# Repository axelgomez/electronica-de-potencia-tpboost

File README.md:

# electronica-de-potencia-tpboost

## Por un lado tenemos el tp flyback (en carpeta homónima)
.pro del Kicad 5.1.X

## Por otro lado tenemos el tp boost
.pro del Kicad 5.1.X

### Nuevas medidas de los componentes a cambiar en el pcb
La primer medida siempre es la distancia entre patas
OK - RL mide 5,5cm por 1cm de ancho y 1cm de alto (1mm de diametro de las patas)
OK - Pines de 2,54mm comunes para popner con jumpers 
OK - Diodo schottky 1,5cm
OK - Capacitor de 470uF 0,5cm. El encapsulado mide 1cm de diametro
OK - Capacitor de 1000uF 0,5cm. El encapsulado mide 1,4cm de diametro
OK - Capacitor de 1nF 0,3cm.
OK - Capacitor de 100nF 0,5cm.
OK - Capacitor de 100pF y 470pF 0,3cm

### Tareas adicionales a realizar:
OK - Agregar resistencias del tamaño de las comunes (1/4W) para sensar corriente en:
	+ Bobina
	+ Capacitor de salida
	+ Diodo schottky
- Hacer agujeros de 3mm para los soportes

## ChangeLog
### Version 28-05-2019 21:10
Se redujo la placa de 10cm x 20cm a 5cm x 10cm.

### Version 28-05-2019 21:55
Se emprolijó el puente de la realimentación, que habia quedado sobre una RQ1.

### Version 29-09-2019 22:52
Se creó el .pro para el tp de flyback y se organizó cada tp en una carpeta diferente

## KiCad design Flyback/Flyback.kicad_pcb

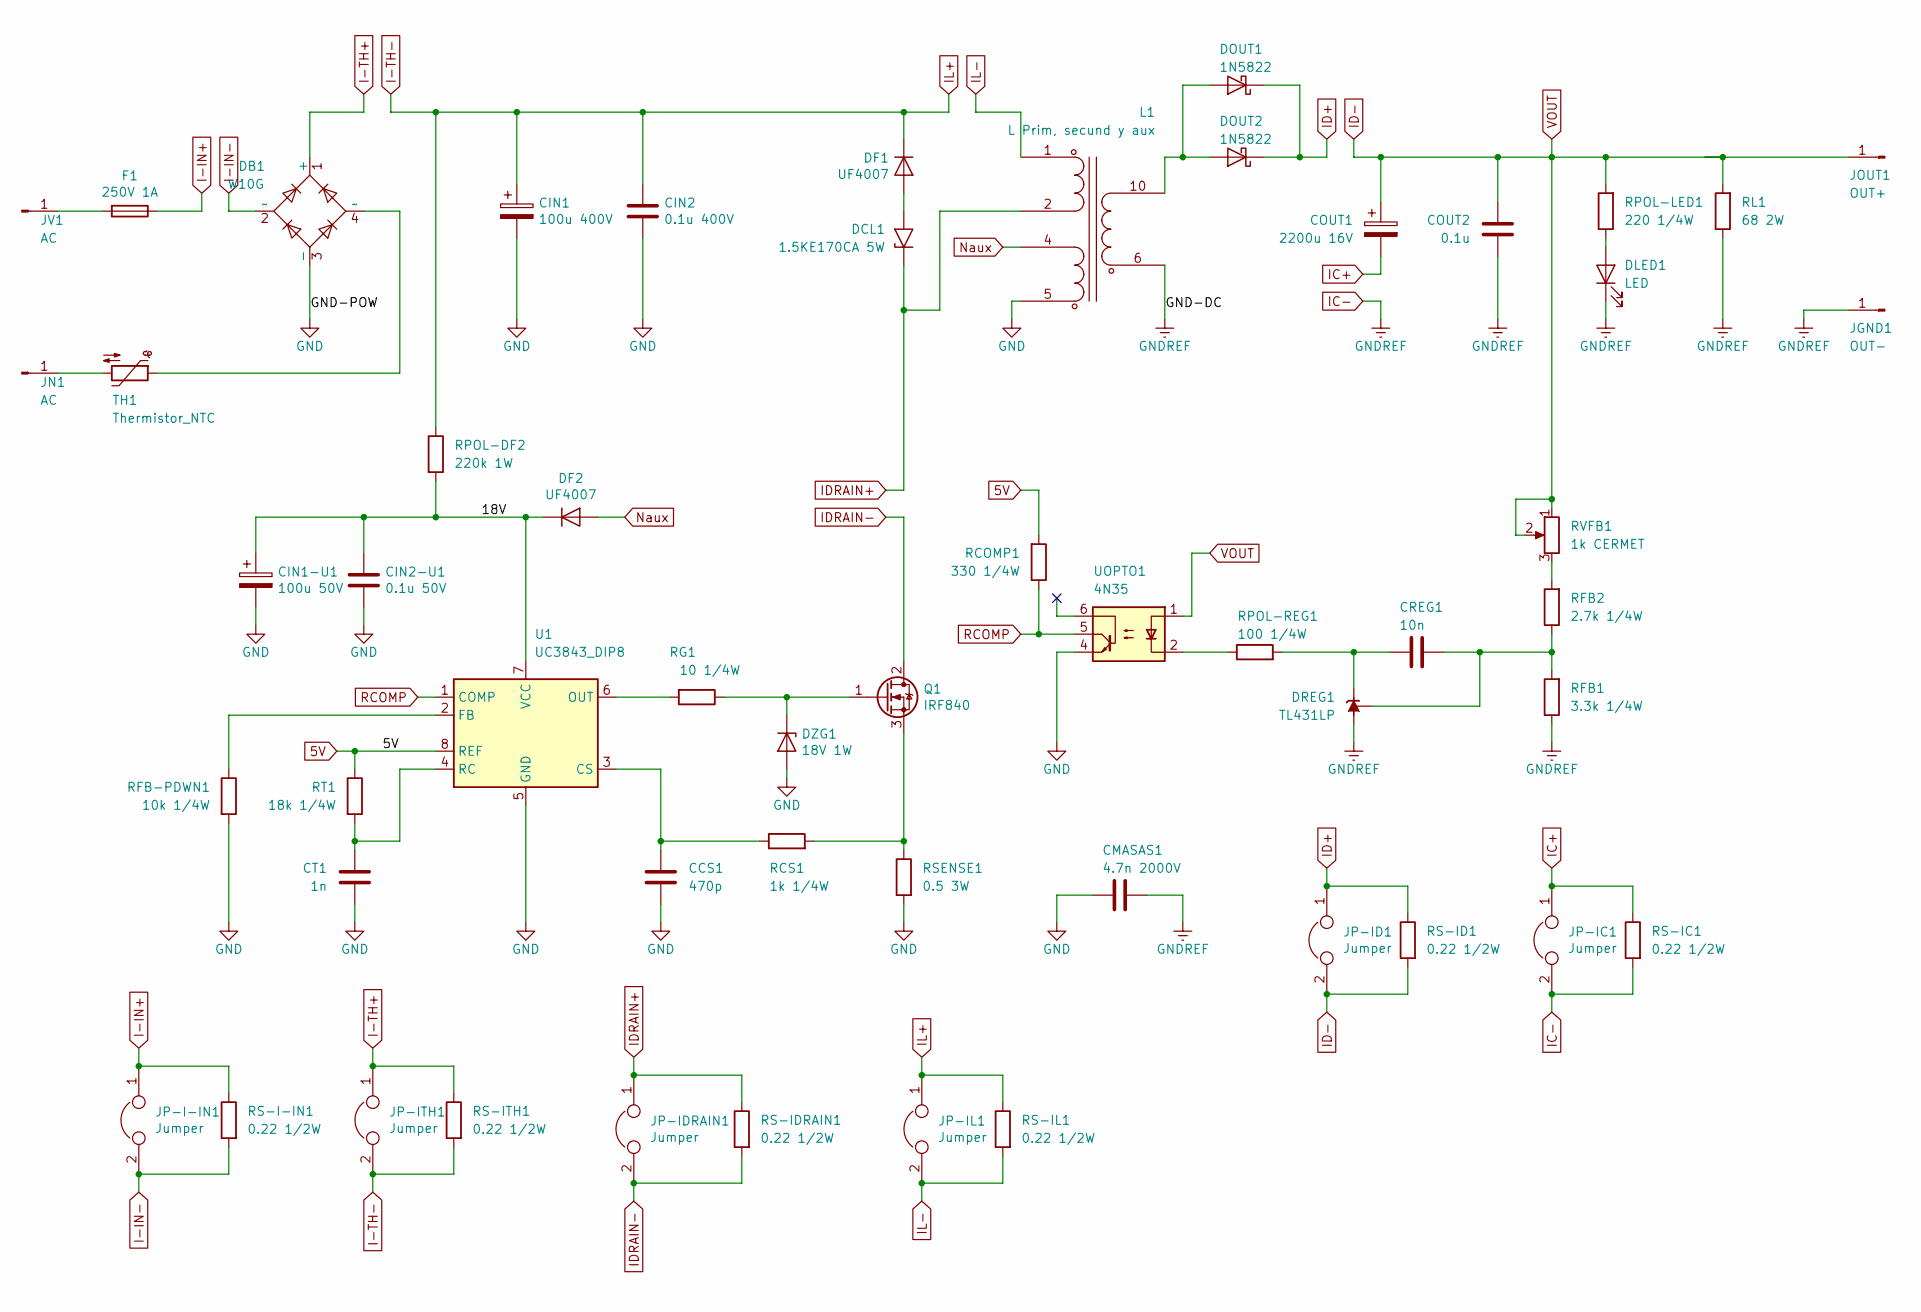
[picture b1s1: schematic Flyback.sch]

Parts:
CCS1: 470p; C_Disc_D3.8mm_W2.6mm_P2.50mm
CIN1: 100u 400V; C_Radial_D18.0mm_H35.5mm_P7.50mm
CIN1-U1: 100u 50V; C_Radial_D8.0mm_H11.5mm_P3.50mm
CIN2: 0.1u 400V; C_Axial_L3.8mm_D2.6mm_P12.50mm_Horizontal
CIN2-U1: 0.1u 50V; C_Disc_D3.8mm_W2.6mm_P2.50mm
CMASAS1: 4.7n 2000V; C_Rect_L9.0mm_W3.2mm_P7.50mm_MKT
COUT1: 2200u 16V; C_Radial_D12.5mm_H25.0mm_P5.00mm
COUT2: 0.1u; C_Disc_D3.8mm_W2.6mm_P2.50mm
CREG1: 10n; C_Rect_L7.2mm_W2.5mm_P5.00mm_FKS2_FKP2_MKS2_MKP2
CT1: 1n; C_Disc_D3.8mm_W2.6mm_P2.50mm
DB1: W10G; PuenteDiodos
DCL1: 1.5KE170CA 5W; D_DO-201AE_P15.24mm_Horizontal
DF1: UF4007; D_DO-41_SOD81_P10.16mm_Horizontal
DF2: UF4007; D_DO-41_SOD81_P12.70mm_Horizontal
DLED1: LED; LED_D5.0mm
DOUT1, DOUT2: 1N5822; D_DO-201AD_P15.24mm_Horizontal
DREG1: TL431LP; TO-92L_Inline_Wide
DZG1: 18V 1W; D_DO-35_SOD27_P10.16mm_Horizontal
F1: 250V 1A; Fuseholder_Cylinder-5x20mm_Stelvio-Kontek_PTF78_Horizontal_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
JGND1: OUT-; Banana_Jack_1Pin
JN1: AC; Banana_Jack_1Pin
JOUT1: OUT+; Banana_Jack_1Pin
JP-I-IN1: Jumper; PinHeader_1x02_P2.54mm_Vertical
JP-IC1: Jumper; PinHeader_1x02_P2.54mm_Vertical
JP-ID1: Jumper; PinHeader_1x02_P2.54mm_Vertical
JP-IDRAIN1: Jumper; PinHeader_1x02_P2.54mm_Vertical
JP-IL1: Jumper; PinHeader_1x02_P2.54mm_Vertical
JP-ITH1: Jumper; PinHeader_1x02_P2.54mm_Vertical
JV1: AC; Banana_Jack_1Pin
L1: L Prim, secund y aux; Trafo-E30157
Q1: IRF840; TO-220-3_Vertical
RCOMP1: 330 1/4W; R_Axial_DIN0207_L6.3mm_D2.5mm_P10.16mm_Horizontal
RCS1: 1k 1/4W; R_Axial_DIN0207_L6.3mm_D2.5mm_P10.16mm_Horizontal
RFB1: 3.3k 1/4W; R_Axial_DIN0309_L9.0mm_D3.2mm_P15.24mm_Horizontal
RFB2: 2.7k 1/4W; R_Axial_DIN0309_L9.0mm_D3.2mm_P15.24mm_Horizontal
RFB-PDWN1: 10k 1/4W; R_Axial_DIN0207_L6.3mm_D2.5mm_P10.16mm_Horizontal
RG1: 10 1/4W; R_Axial_DIN0207_L6.3mm_D2.5mm_P10.16mm_Horizontal
RL1: 68 2W; RCarga30mm
RPOL-DF2: 220k 1W; R12,5
RPOL-LED1: 220 1/4W; R_Axial_DIN0207_L6.3mm_D2.5mm_P10.16mm_Horizontal
RPOL-REG1: 100 1/4W; R_Axial_DIN0309_L9.0mm_D3.2mm_P15.24mm_Horizontal
RS-I-IN1: 0.22 1/2W; R_Axial_DIN0309_L9.0mm_D3.2mm_P15.24mm_Horizontal
RS-IC1: 0.22 1/2W; R_Axial_DIN0309_L9.0mm_D3.2mm_P15.24mm_Horizontal
RS-ID1: 0.22 1/2W; R_Axial_DIN0309_L9.0mm_D3.2mm_P15.24mm_Horizontal
RS-IDRAIN1: 0.22 1/2W; R_Axial_DIN0309_L9.0mm_D3.2mm_P15.24mm_Horizontal
RS-IL1: 0.22 1/2W; R_Axial_DIN0309_L9.0mm_D3.2mm_P15.24mm_Horizontal
RS-ITH1: 0.22 1/2W; R_Axial_DIN0309_L9.0mm_D3.2mm_P15.24mm_Horizontal
RSENSE1: 0.5 3W; R_Axial_DIN0309_L9.0mm_D3.2mm_P15.24mm_Horizontal
RT1: 18k 1/4W; R_Axial_DIN0207_L6.3mm_D2.5mm_P10.16mm_Horizontal
RVFB1: 1k CERMET; Potentiometer_Bourns_3266Y_Vertical
TH1: Thermistor_NTC; R_Axial_DIN0207_L6.3mm_D2.5mm_P2.54mm_Vertical
U1: UC3843_DIP8; DIP-8_W7.62mm
UOPTO1: 4N35; DIP-6_W7.62mm

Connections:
5V: RCOMP1.2, RT1.1, U1.8 (REF)
/18V: CIN1-U1.1, CIN2-U1.1, DF2.1 (K), RPOL-DF2.2, U1.7 (VCC)
GND: CCS1.2, CIN1.2, CIN1-U1.2, CIN2.2, CIN2-U1.2, CMASAS1.1, CT1.2, DB1.3 (-), DZG1.2 (A), L1.5, RFB-PDWN1.2, RSENSE1.2, U1.5 (GND), UOPTO1.4
I-IN+: F1.1, JP-I-IN1.1, RS-I-IN1.1
I-IN-: DB1.2 (~~), JP-I-IN1.2, RS-I-IN1.2
I-TH+: DB1.1 (+), JP-ITH1.1, RS-ITH1.1
I-TH-: CIN1.1, CIN2.1, DF1.1 (K), JP-IL1.1, JP-ITH1.2, RPOL-DF2.1, RS-IL1.1, RS-ITH1.2
IC+: COUT1.2, JP-IC1.1, RS-IC1.1
IC-: CMASAS1.2, COUT2.2, DLED1.1 (K), DREG1.2 (A), JGND1.1, JP-IC1.2, L1.6, RFB1.1, RL1.1, RS-IC1.2
ID+: DOUT1.1 (K), DOUT2.1 (K), JP-ID1.1, RS-ID1.1
ID-: COUT1.1, COUT2.1, JOUT1.1, JP-ID1.2, RL1.2, RPOL-LED1.2, RS-ID1.2, RVFB1.1, RVFB1.2, UOPTO1.1
IDRAIN+: DCL1.1 (A1), JP-IDRAIN1.1, L1.2, RS-IDRAIN1.1
IDRAIN-: JP-IDRAIN1.2, Q1.2 (D), RS-IDRAIN1.2
IL-: JP-IL1.2, L1.1, RS-IL1.2
Naux: DF2.2 (A), L1.4
unnamed: CCS1.1, RCS1.1, U1.3 (CS)
unnamed: CREG1.1, DREG1.3 (K), RPOL-REG1.2
unnamed: CREG1.2, DREG1.1 (REF), RFB1.2, RFB2.1
unnamed: CT1.1, RT1.2, U1.4 (RC)
unnamed: DB1.4 (~~), TH1.1
unnamed: DCL1.2 (A2), DF1.2 (A)
unnamed: DLED1.2 (A), RPOL-LED1.1
unnamed: DOUT1.2 (A), DOUT2.2 (A), L1.10
unnamed: DZG1.1 (K), Q1.1 (G), RG1.1
unnamed: F1.2, JV1.1
unnamed: JN1.1, TH1.2
unnamed: Q1.3 (S), RCS1.2, RSENSE1.1
unnamed: RFB2.2, RVFB1.3
unnamed: RFB-PDWN1.1, U1.2 (FB)
unnamed: RG1.2, U1.6 (OUT)
unnamed: RPOL-REG1.1, UOPTO1.2
RCOMP: RCOMP1.1, U1.1 (COMP), UOPTO1.5

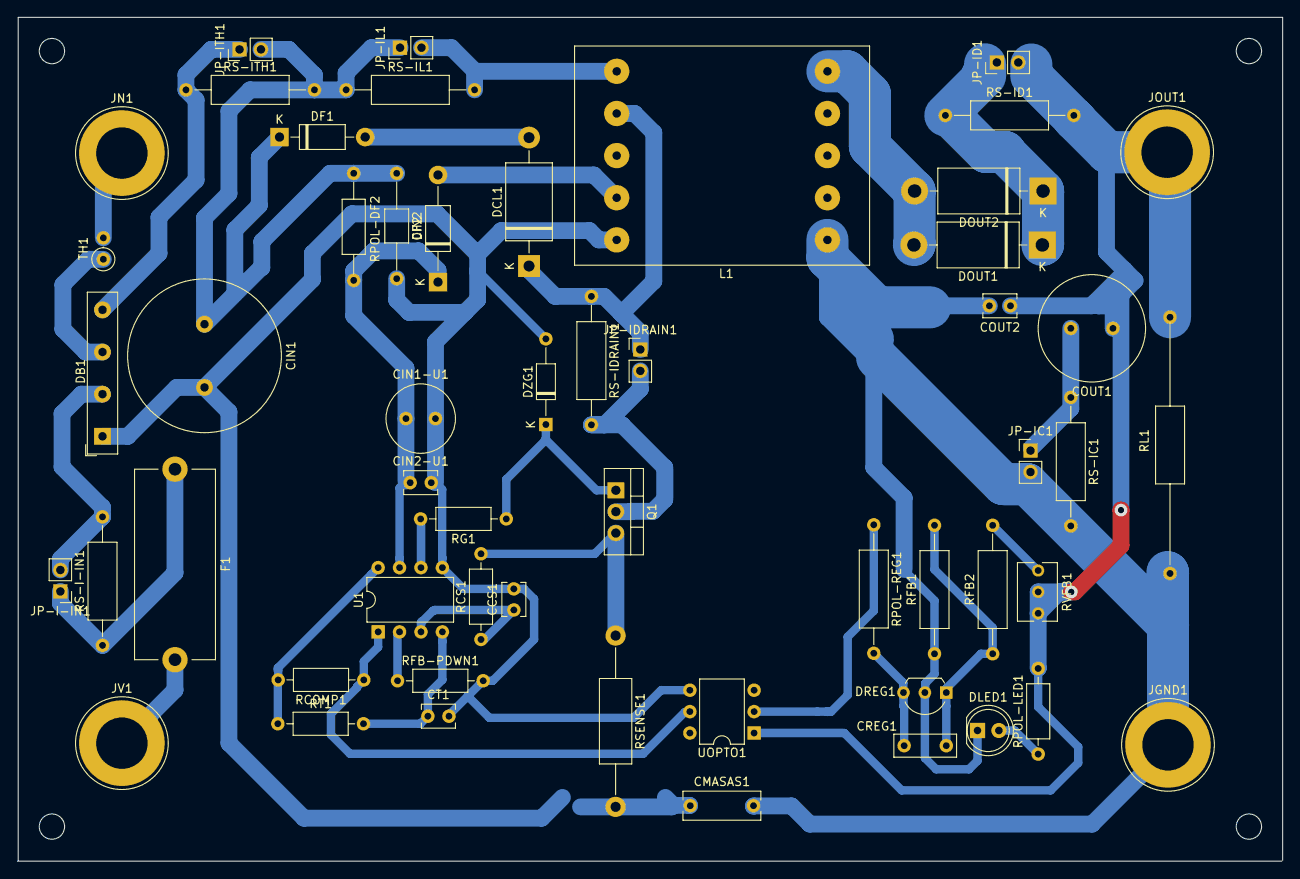
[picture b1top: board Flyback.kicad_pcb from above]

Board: 2 copper layers, 150.1 x 100.1 mm, 54 parts (0 on the bottom side), 32 nets.

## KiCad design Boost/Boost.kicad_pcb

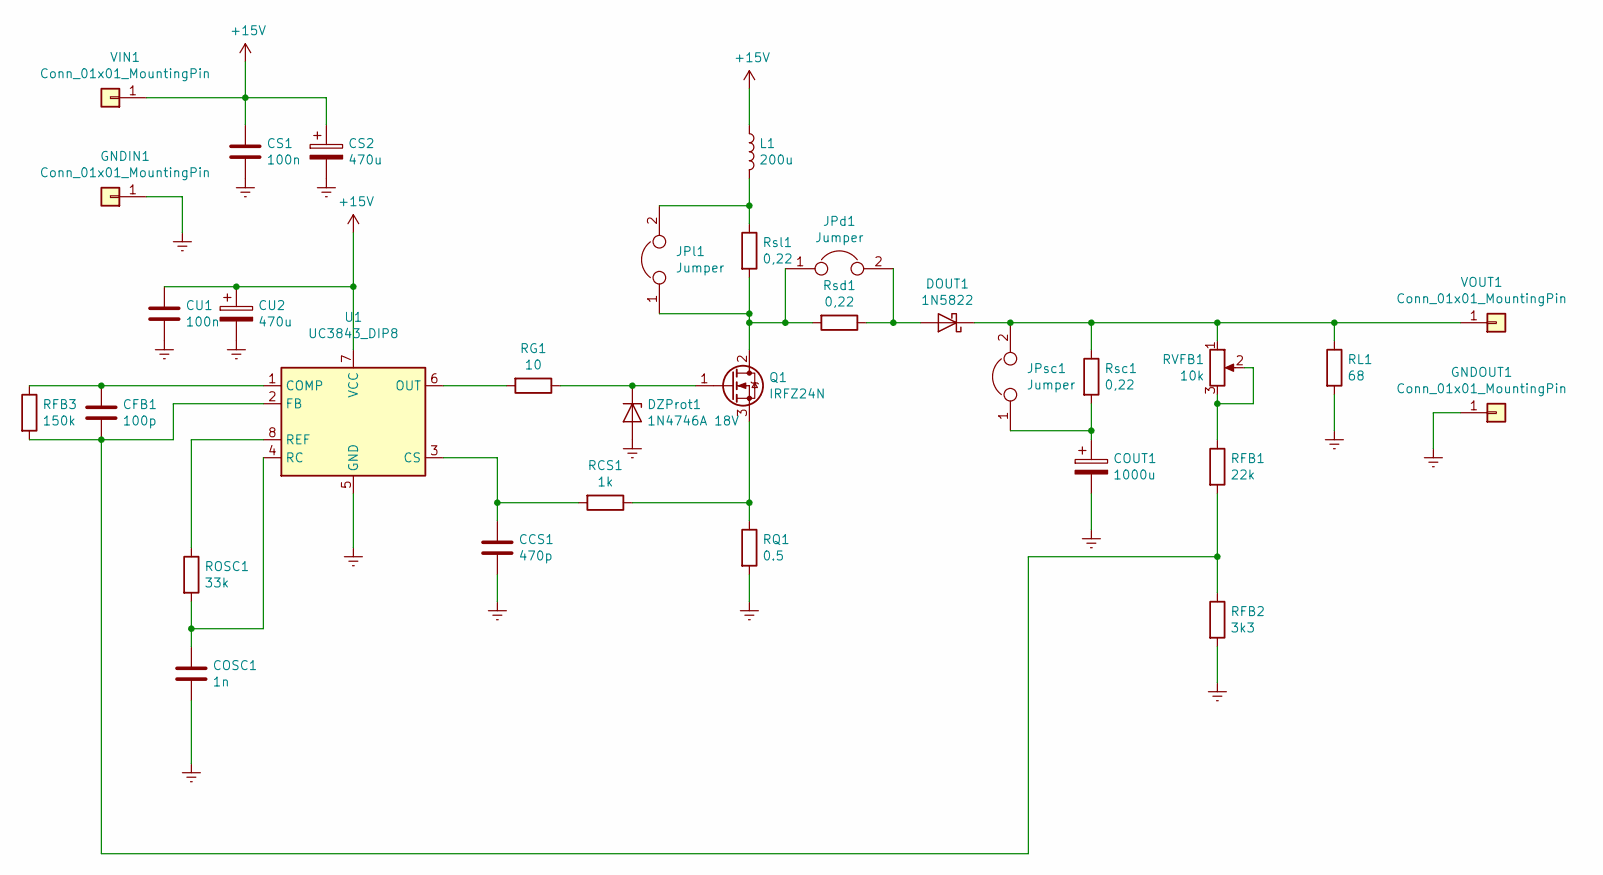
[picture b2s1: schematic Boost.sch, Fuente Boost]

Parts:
CCS1: 470p; C_Disc_D3.0mm_W2.0mm_P2.50mm
CFB1: 100p; C_Disc_D3.0mm_W2.0mm_P2.50mm
COSC1: 1n; C_Disc_D3.4mm_W2.1mm_P2.50mm
COUT1: 1000u; CP_Radial_D14.0mm_P5.00mm
CS1: 100n; C_Disc_D4.7mm_W2.5mm_P5.00mm
CS2: 470u; CP_Radial_D10.0mm_P5.00mm
CU1: 100n; C_Disc_D4.7mm_W2.5mm_P5.00mm
CU2: 470u; CP_Radial_D10.0mm_P5.00mm
DOUT1: 1N5822; D_DO-41_SOD81_P12.70mm_Horizontal
DZProt1: 1N4746A 18V; D_DO-41_SOD81_P10.16mm_Horizontal
GNDIN1: Conn_01x01_MountingPin; Banana_Jack_1Pin
GNDOUT1: Conn_01x01_MountingPin; Banana_Jack_1Pin
JPd1: Jumper; PinHeader_1x02_P2.54mm_Vertical
JPl1: Jumper; PinHeader_1x02_P2.54mm_Vertical
JPsc1: Jumper; PinHeader_1x02_P2.54mm_Vertical
L1: 200u; Inductor_26mm_x_8mm
Q1: IRFZ24N; TO-220-3_Vertical
RCS1: 1k; R_Axial_DIN0207_L6.3mm_D2.5mm_P10.16mm_Horizontal
RFB1: 22k; R_Axial_DIN0207_L6.3mm_D2.5mm_P10.16mm_Horizontal
RFB2: 3k3; R_Axial_DIN0207_L6.3mm_D2.5mm_P10.16mm_Horizontal
RFB3: 150k; R_Axial_DIN0207_L6.3mm_D2.5mm_P10.16mm_Horizontal
RG1: 10; R_Axial_DIN0207_L6.3mm_D2.5mm_P10.16mm_Horizontal
RL1: 68; R_Axial_Power_L50.0mm_W9.0mm_P60.96mm
ROSC1: 33k; R_Axial_DIN0207_L6.3mm_D2.5mm_P10.16mm_Horizontal
RQ1: 0.5; R_Axial_DIN0207_L6.3mm_D2.5mm_P10.16mm_Horizontal
RVFB1: 10k; Potentiometer_Bourns_3266Y_Vertical
Rsc1: 0,22; R_Axial_DIN0207_L6.3mm_D2.5mm_P10.16mm_Horizontal
Rsd1: 0,22; R_Axial_DIN0207_L6.3mm_D2.5mm_P10.16mm_Horizontal
Rsl1: 0,22; R_Axial_DIN0207_L6.3mm_D2.5mm_P10.16mm_Horizontal
U1: UC3843_DIP8; DIP-8_W7.62mm
VIN1: Conn_01x01_MountingPin; Banana_Jack_1Pin
VOUT1: Conn_01x01_MountingPin; Banana_Jack_1Pin

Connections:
+15V: CS1.1, CS2.1, CU1.1, CU2.1, L1.1, U1.7 (VCC), VIN1.1
Earth: CCS1.2, COSC1.2, COUT1.2, CS1.2, CS2.2, CU1.2, CU2.2, DZProt1.2 (A), GNDIN1.1, GNDOUT1.1, RFB2.2, RL1.2, RQ1.2, U1.5 (GND)
unnamed: CCS1.1, RCS1.2, U1.3 (CS)
unnamed: CFB1.1, RFB3.1, U1.1 (COMP)
unnamed: CFB1.2, RFB1.2, RFB2.1, RFB3.2, U1.2 (FB)
unnamed: COSC1.1, ROSC1.2, U1.4 (RC)
unnamed: COUT1.1, JPsc1.1, Rsc1.2
unnamed: DOUT1.1 (K), JPsc1.2, RL1.1, RVFB1.1, Rsc1.1, VOUT1.1
unnamed: DOUT1.2 (A), JPd1.2, Rsd1.1
unnamed: DZProt1.1 (K), Q1.1 (G), RG1.1
unnamed: JPd1.1, JPl1.1, Q1.2 (D), Rsd1.2, Rsl1.2
unnamed: JPl1.2, L1.2, Rsl1.1
unnamed: Q1.3 (S), RCS1.1, RQ1.1
unnamed: RFB1.1, RVFB1.2, RVFB1.3
unnamed: RG1.2, U1.6 (OUT)
unnamed: ROSC1.1, U1.8 (REF)

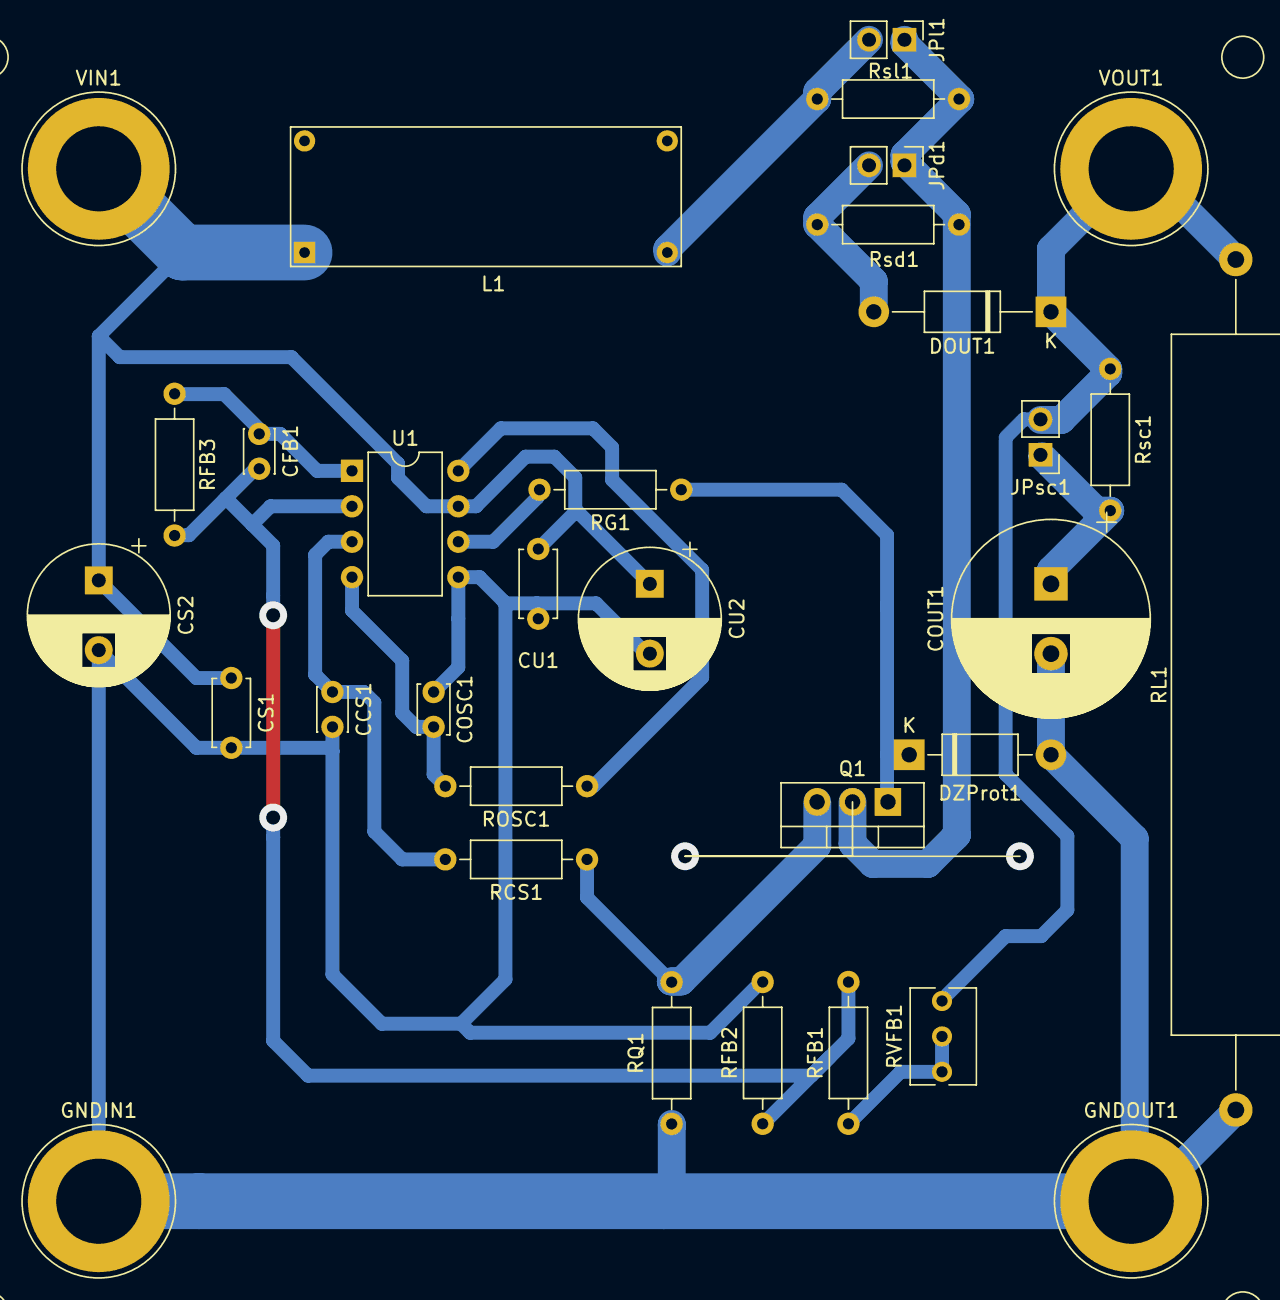
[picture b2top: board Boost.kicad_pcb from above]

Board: 2 copper layers, 32 parts (0 on the bottom side), 16 nets.

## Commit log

2019-05-28 agregado rpot a la salida
2019-05-29 Reducción de placa
    Se redujo la placa de 10cm x 20cm a 5cm x 10 cm.
2019-05-29 Emprolijando el puente de feedback
    Emprolije el puente de la realimentación, que habia quedado sobre una RQ1.
2019-05-31 Actualización de placa y titulo
2019-06-03 Modificado PCB y esquemático según clase del 31/06/19
2019-06-04 reemplazado IRFZ44N por IRFZ24N
2019-06-14 modificado esquematico y pcb, pero falta modificar pcb
2019-06-16 acomodado pcb a 10x10 con bobina casi de la medida y disipador del FET, resta corroborar medidas de los mismos
2019-06-19 Disipador + Bobina.
2019-06-20 Version real hecha
2019-09-29 agregado flyback vacio
2019-09-30 agregado esquematico Flyback
2019-09-30 agregado Flyback
2019-09-30 fixeado segun el esquematico que paso el prof
2019-09-30 arreglos menores
2019-10-03 primeros pasos del pcb
2019-10-04 agregados packages de los componentes
2019-10-04 Listo
    Listo para el route
2019-10-04 autoruteado
2019-10-06 PCB_v0
2019-10-06 PCB_v1
2019-10-13 revisado layout 20191013
2019-10-13 ploteado version 0.2.pdf con edgecuts
2019-10-13 ploteado 0.2byn.pdf
2019-10-13 ploteado solo el back y edgecuts (sin front)
2019-10-24 agrandado la Rsense de 3W a 20.32mm de largo y retoques minimos
